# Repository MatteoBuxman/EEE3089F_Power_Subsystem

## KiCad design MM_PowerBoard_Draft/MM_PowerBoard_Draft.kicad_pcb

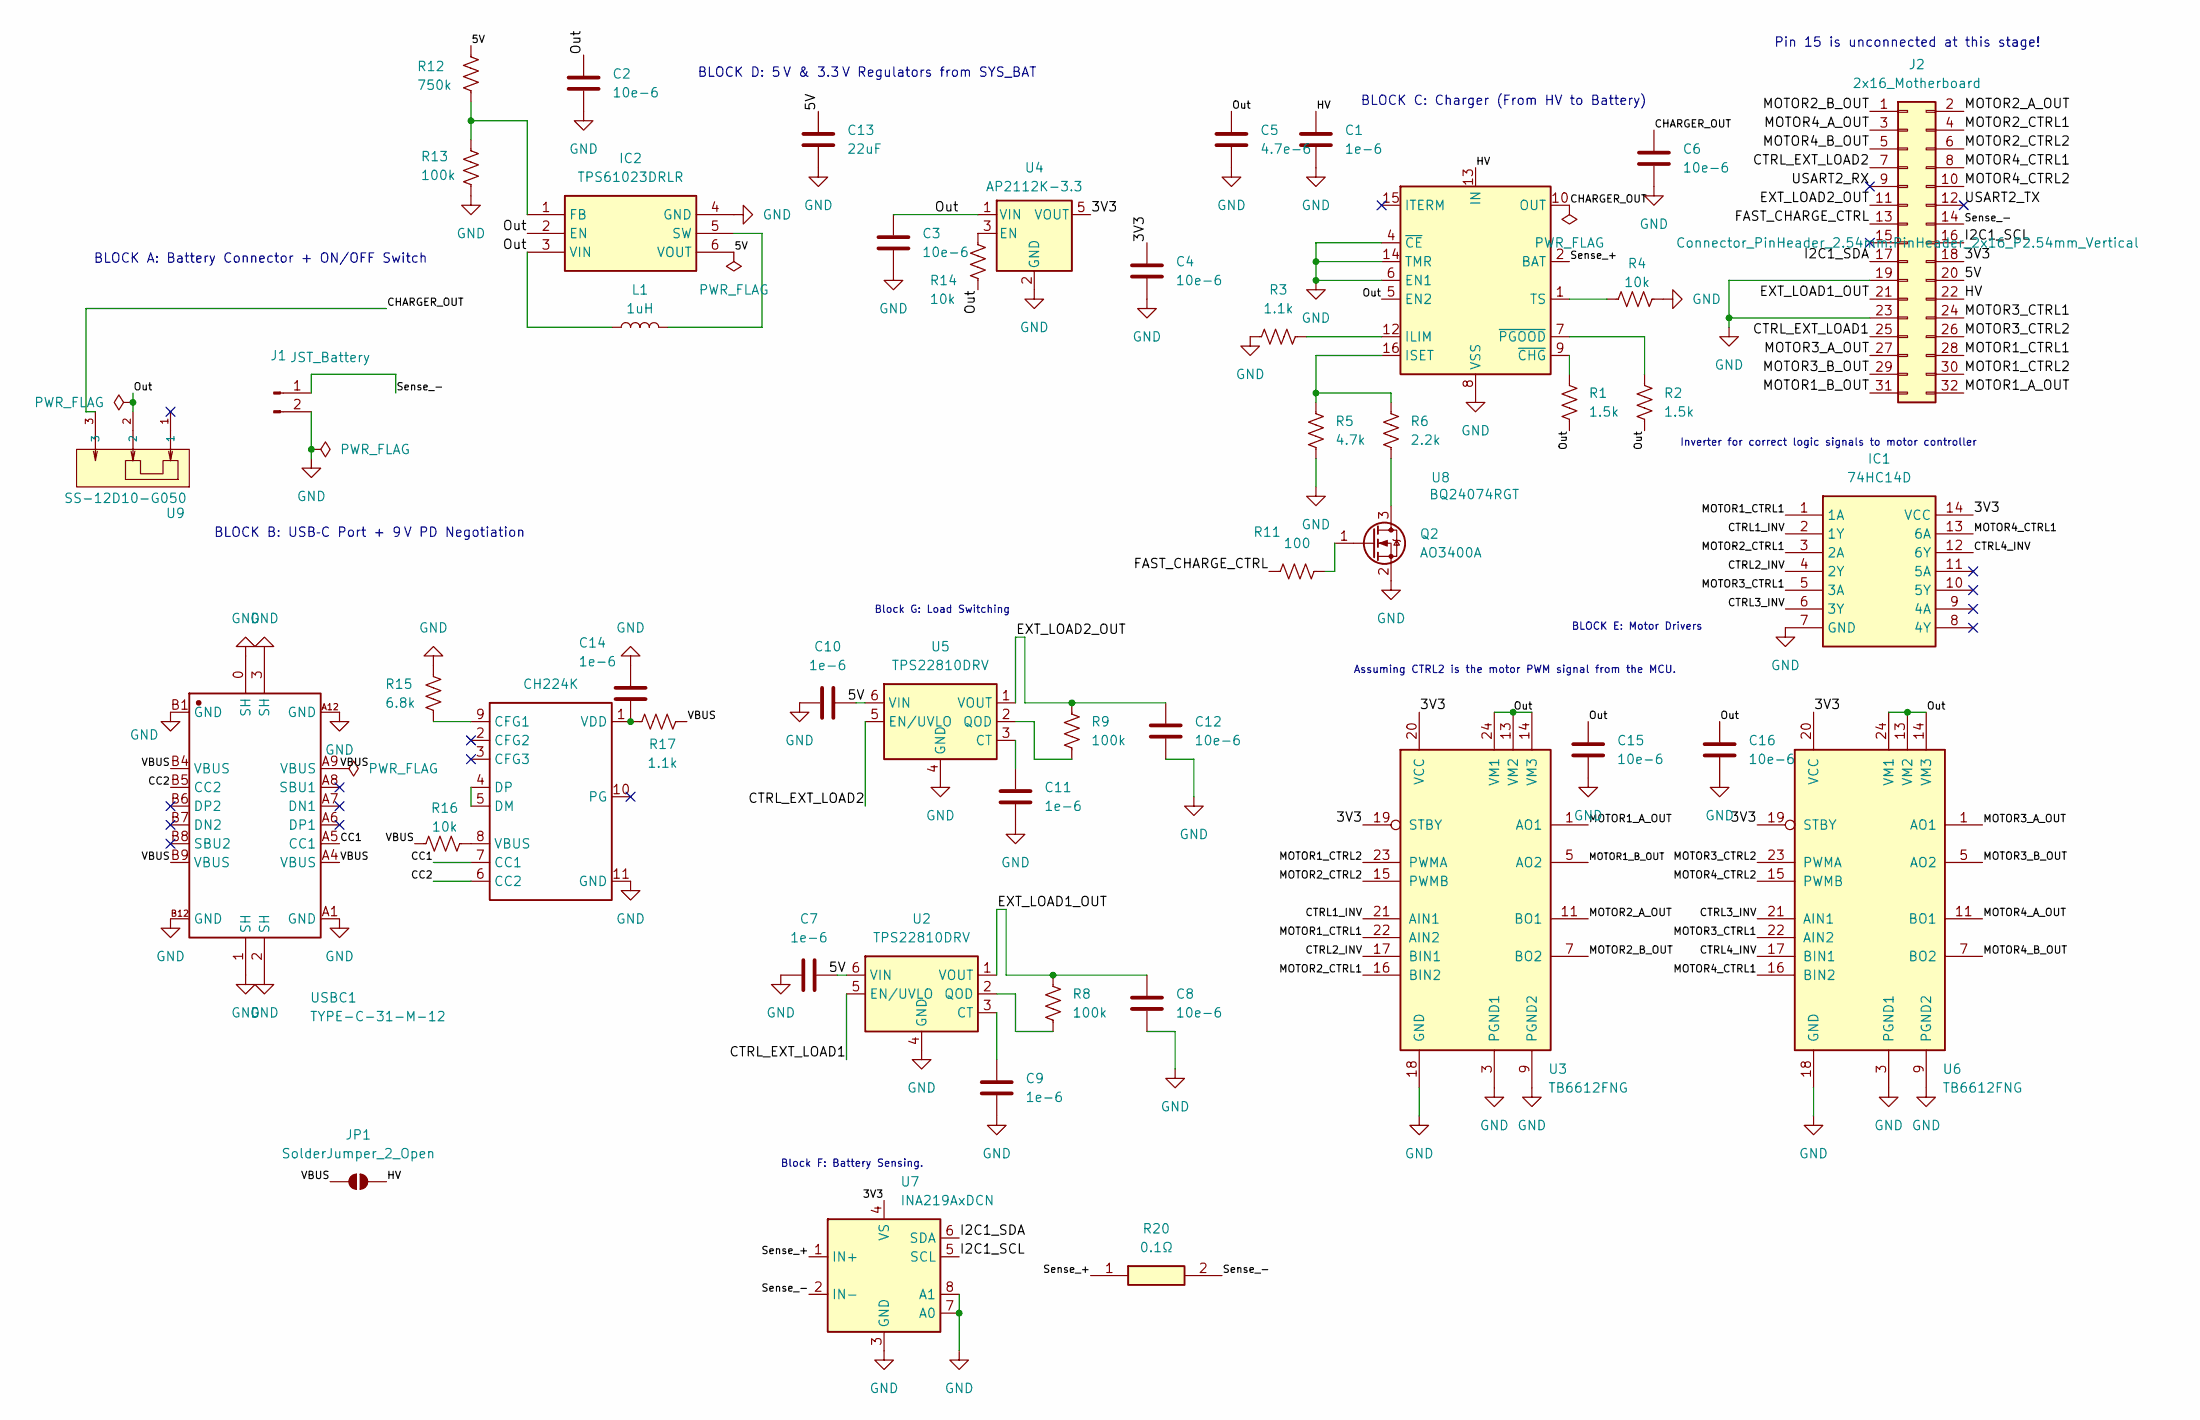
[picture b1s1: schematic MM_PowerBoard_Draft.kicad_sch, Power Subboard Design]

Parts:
C1, C7, C9, C10, C11, C14: 1e-6; C0603
C2, C3, C4, C6, C8, C12, C15, C16: 10e-6; C0603
C5: 4.7e-6; C0603
C13: 22uF; C1206
IC1: 74HC14D; SOIC-14_L8.7-W3.9-P1.27-LS6.0-BL; Manufacturer_Part_Number 74HC14D; Mouser Part Number 771-74HC14D
IC2: TPS61023DRLR; SOT-563_L1.6-W1.2-P0.50-LS1.6-BR; Manufacturer_Part_Number TPS61023DRLR; Mouser Part Number 595-TPS61023DRLR
J1: JST_Battery; JST_PH_S2B-PH-SM4-TB_1x02-1MP_P2.00mm_Horizontal
J2: 2x16_Motherboard; PinHeader_2x16_P2.54mm_Vertical
JP1: SolderJumper_2_Open; SolderJumper-2_P1.3mm_Open_Pad1.0x1.5mm
L1: 1uH; L_Sunlord_SWPA4030S
Q2: AO3400A; SOT-23-3_L2.9-W1.3-P1.90-LS2.4-BR
R1, R2: 1.5k; R0603
R3, R17: 1.1k; R0603
R4, R14, R16: 10k; R0603
R5: 4.7k; R0603
R6: 2.2k; R0603
R8, R9: 100k; R0603
R11: 100; R0603
R12: 750k; R0603
R13: 100k; R1206
R15: 6.8k; R0603
R20: 0.1Ω; R2512; Manufacturer_Part_Number PE2512FKE7W0R1L
U1: CH224K; ESSOP-10_L4.9-W3.9-P1.0-LS6.0-TL-EP; Manufacturer Part CH224K
U2, U5: TPS22810DRV; WSON-6-1EP_2x2mm_P0.65mm_EP1x1.6mm
U3, U6: TB6612FNG; SSOP-24_5.3x8.2mm_P0.65mm
U4: AP2112K-3.3; SOT-25-5_L2.9-W1.6-P0.95-LS2.8-BL
U7: INA219AxDCN; SOT-23-8
U8: BQ24074RGT; VQFN-16_L3.0-W3.0-P0.50-TL-EP1.7
U9: SS-12D10-G050; SW-TH_SS-12D10-G050; LCSC C2848933
USBC1: TYPE-C-31-M-12; USB-C_SMD-TYPE-C-31-M-12; Manufacturer Part TYPE-C-31-M-12

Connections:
/3V3: C4.1, IC1.14 (VCC), J2.18, U3.19 (STBY), U3.20 (VCC), U4.5 (VOUT), U6.19 (STBY), U6.20 (VCC), U7.4 (VS)
/5V: C7.2, C10.2, C13.1, IC2.6 (VOUT), J2.20, R12.1, U2.6 (VIN), U5.6 (VIN)
/CC1: U1.7 (CC1), USBC1.A5 (CC1)
/CC2: U1.6 (CC2), USBC1.B5 (CC2)
/CHARGER_OUT: C6.1, U8.10 (OUT), U8.11 (OUT), U9.3
/CTRL1_INV: IC1.2 (1Y), U3.21 (AIN1)
/CTRL2_INV: IC1.4 (2Y), U3.17 (BIN1)
/CTRL3_INV: IC1.6 (3Y), U6.21 (AIN1)
/CTRL4_INV: IC1.12 (6Y), U6.17 (BIN1)
/CTRL_EXT_LOAD1: J2.25, U2.5 (EN/UVLO)
/CTRL_EXT_LOAD2: J2.7, U5.5 (EN/UVLO)
/EXT_LOAD1_OUT: C8.1, J2.21, R8.1, U2.1 (VOUT)
/EXT_LOAD2_OUT: C12.1, J2.11, R9.1, U5.1 (VOUT)
/FAST_CHARGE_CTRL: J2.13, R11.1
/HV: C1.1, J2.22, JP1.2 (B), U8.13 (IN)
/I2C1_SCL: J2.16, U7.5 (SCL)
/I2C1_SDA: J2.17, U7.6 (SDA)
/MOTOR1_A_OUT: J2.32, U3.1 (AO1), U3.2 (AO1)
/MOTOR1_B_OUT: J2.31, U3.5 (AO2), U3.6 (AO2)
/MOTOR1_CTRL1: IC1.1 (1A), J2.28, U3.22 (AIN2)
/MOTOR1_CTRL2: J2.30, U3.23 (PWMA)
/MOTOR2_A_OUT: J2.2, U3.11 (BO1), U3.12 (BO1)
/MOTOR2_B_OUT: J2.1, U3.7 (BO2), U3.8 (BO2)
/MOTOR2_CTRL1: IC1.3 (2A), J2.4, U3.16 (BIN2)
/MOTOR2_CTRL2: J2.6, U3.15 (PWMB)
/MOTOR3_A_OUT: J2.27, U6.1 (AO1), U6.2 (AO1)
/MOTOR3_B_OUT: J2.29, U6.5 (AO2), U6.6 (AO2)
/MOTOR3_CTRL1: IC1.5 (3A), J2.24, U6.22 (AIN2)
/MOTOR3_CTRL2: J2.26, U6.23 (PWMA)
/MOTOR4_A_OUT: J2.3, U6.11 (BO1), U6.12 (BO1)
/MOTOR4_B_OUT: J2.5, U6.7 (BO2), U6.8 (BO2)
/MOTOR4_CTRL1: IC1.13 (6A), J2.8, U6.16 (BIN2)
/MOTOR4_CTRL2: J2.10, U6.15 (PWMB)
/Out: C2.1, C3.1, C5.1, C15.1, C16.1, IC2.2 (EN), IC2.3 (VIN), L1.1, R1.2, R2.2, R14.2, U3.13 (VM2), U3.14 (VM3), U3.24 (VM1), U4.1 (VIN), U6.13 (VM2), U6.14 (VM3), U6.24 (VM1), U8.5 (EN2), U9.2
/Sense_+: R20.1, U7.1 (IN+), U8.2 (BAT), U8.3 (BAT)
/Sense_-: J1.1, J2.14, R20.2, U7.2 (IN-)
/USART2_RX: J2.9
/USART2_TX: J2.12
/VBUS: JP1.1 (A), R16.1, R17.1, USBC1.A4 (VBUS), USBC1.A9 (VBUS), USBC1.B4 (VBUS), USBC1.B9 (VBUS)
GND: C1.2, C2.2, C3.2, C4.2, C5.2, C6.2, C7.1, C8.2, C9.2, C10.1, C11.2, C12.2, C13.2, C14.2, C15.2, C16.2, IC1.7 (GND), IC2.4 (GND), J1.2, J2.19, J2.23, Q2.2 (S), R3.1, R4.2, R5.2, R13.2, R15.1, U1.11 (GND), U2.4 (GND), U2.7 (GND), U3.3 (PGND1), U3.4 (PGND1), U3.9 (PGND2), U3.10 (PGND2), U3.18 (GND), U4.2 (GND), U5.4 (GND), U5.7 (GND), U6.3 (PGND1), U6.4 (PGND1), U6.9 (PGND2), U6.10 (PGND2), U6.18 (GND), U7.3 (GND), U7.7 (A0), U7.8 (A1), U8.4 (~CE), U8.6 (EN1), U8.8 (VSS), U8.14 (TMR), U8.17 (VSS), USBC1.0 (SH), USBC1.1 (SH), USBC1.2 (SH), USBC1.3 (SH), USBC1.A1 (GND), USBC1.A12 (GND), USBC1.B1 (GND), USBC1.B12 (GND)
unnamed: IC2.1 (FB), R12.2, R13.1
unnamed: IC2.5 (SW), L1.2
unnamed: Q2.3 (D), R6.2
unnamed: Q2.1 (G), R11.2
unnamed: R15.2, U1.9 (CFG1)
unnamed: U1.4 (DP), U1.5 (DM)
unnamed: R16.2, U1.8 (VBUS)
unnamed: C14.1, R17.2, U1.1 (VDD)
unnamed: C9.1, U2.3 (CT)
unnamed: R8.2, U2.2 (QOD)
unnamed: R14.1, U4.3 (EN)
unnamed: C11.1, U5.3 (CT)
unnamed: R9.2, U5.2 (QOD)
unnamed: R3.2, U8.12 (ILIM)
unnamed: R5.1, R6.1, U8.16 (ISET)
unnamed: R4.1, U8.1 (TS)
unnamed: R1.1, U8.9 (~CHG)
unnamed: R2.1, U8.7 (~PGOOD)

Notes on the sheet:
BLOCK E: Motor Drivers
BLOCK D: 5 V & 3.3 V Regulators from SYS_BAT
Assuming CTRL2 is the motor PWM signal from the MCU.
BLOCK C: Charger (From HV to Battery)
Block F: Battery Sensing.
BLOCK B: USB‐C Port + 9 V PD Negotiation
BLOCK A: Battery Connector + ON/OFF Switch
Pin 15 is unconnected at this stage!
Block G: Load Switching
Inverter for correct logic signals to motor controller

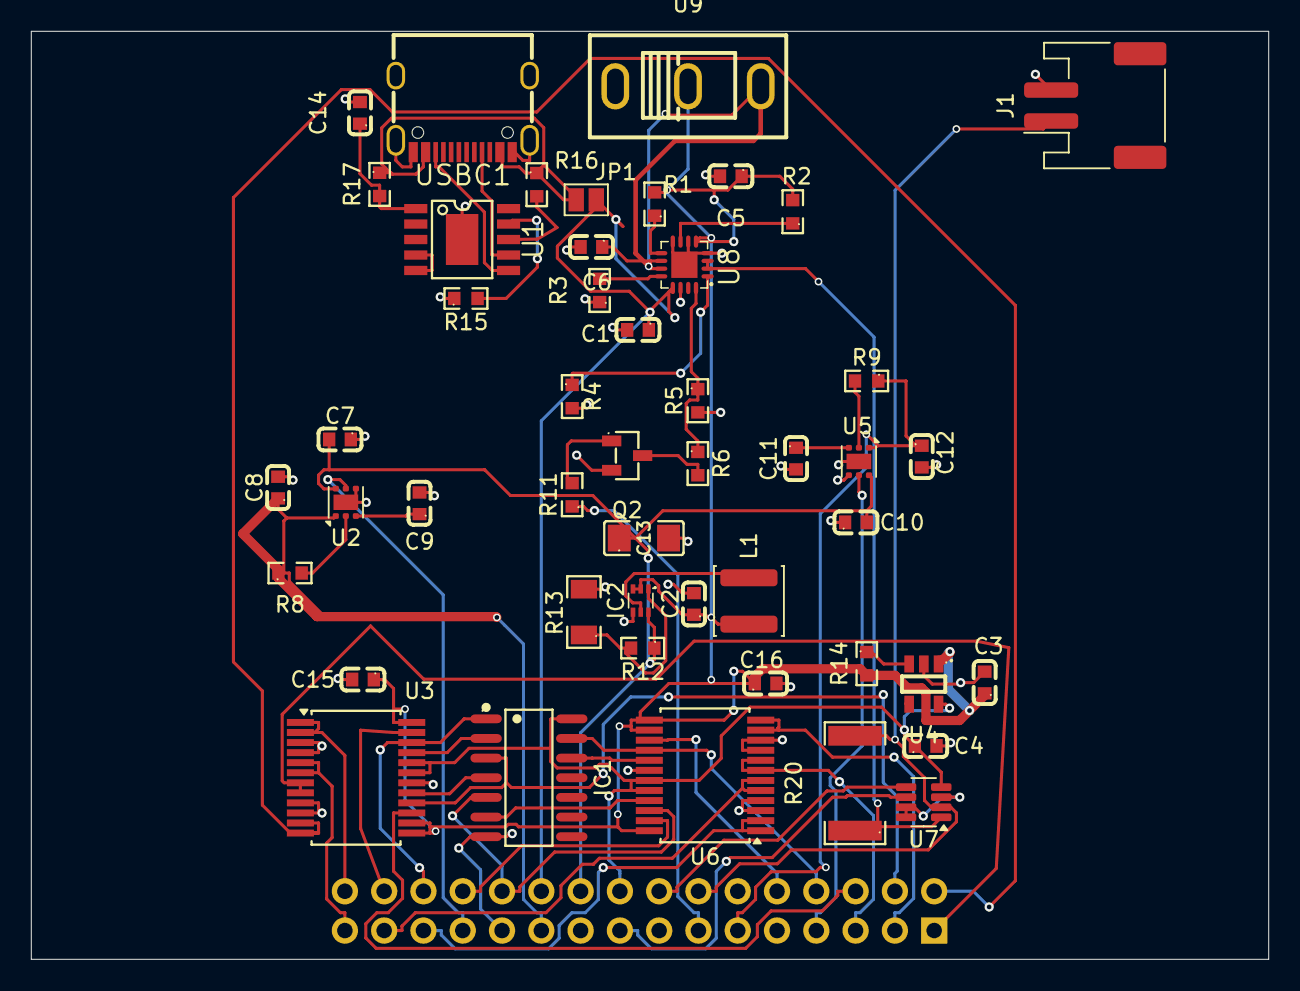
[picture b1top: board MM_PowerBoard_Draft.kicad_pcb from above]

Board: 2 copper layers, 80.0 x 60.0 mm, 49 parts (1 on the bottom side), 56 nets.

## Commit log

2025-03-22 Initial Commit 2
2025-03-23 Add KiCad project for power board
2025-03-24 Added preliminary 1. Motor Drivers 2. Battery Sensing 3. Board Header
2025-03-25 Added battery charger which handles load switch over when external power source is plugged in.
2025-03-25 gonna push again
2025-03-25 testing
2025-03-25 Load switching fixed
2025-03-25 Fixed some stuff
2025-03-25 Added some footprints
2025-03-27 PCB in progress.
2025-03-28 Few violations left
2025-03-28 Almost there
2025-03-28 Latest
